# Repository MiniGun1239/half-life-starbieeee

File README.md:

# half-life-starbieeee
Starbie Project for the YSWS Half Life

## What is this
Well, its just a starbie, except shaped like a very badly shaped rocket and a rotary encoder is added.

Its your own PCB Pet... a PetCB

## PCB routing and stuff

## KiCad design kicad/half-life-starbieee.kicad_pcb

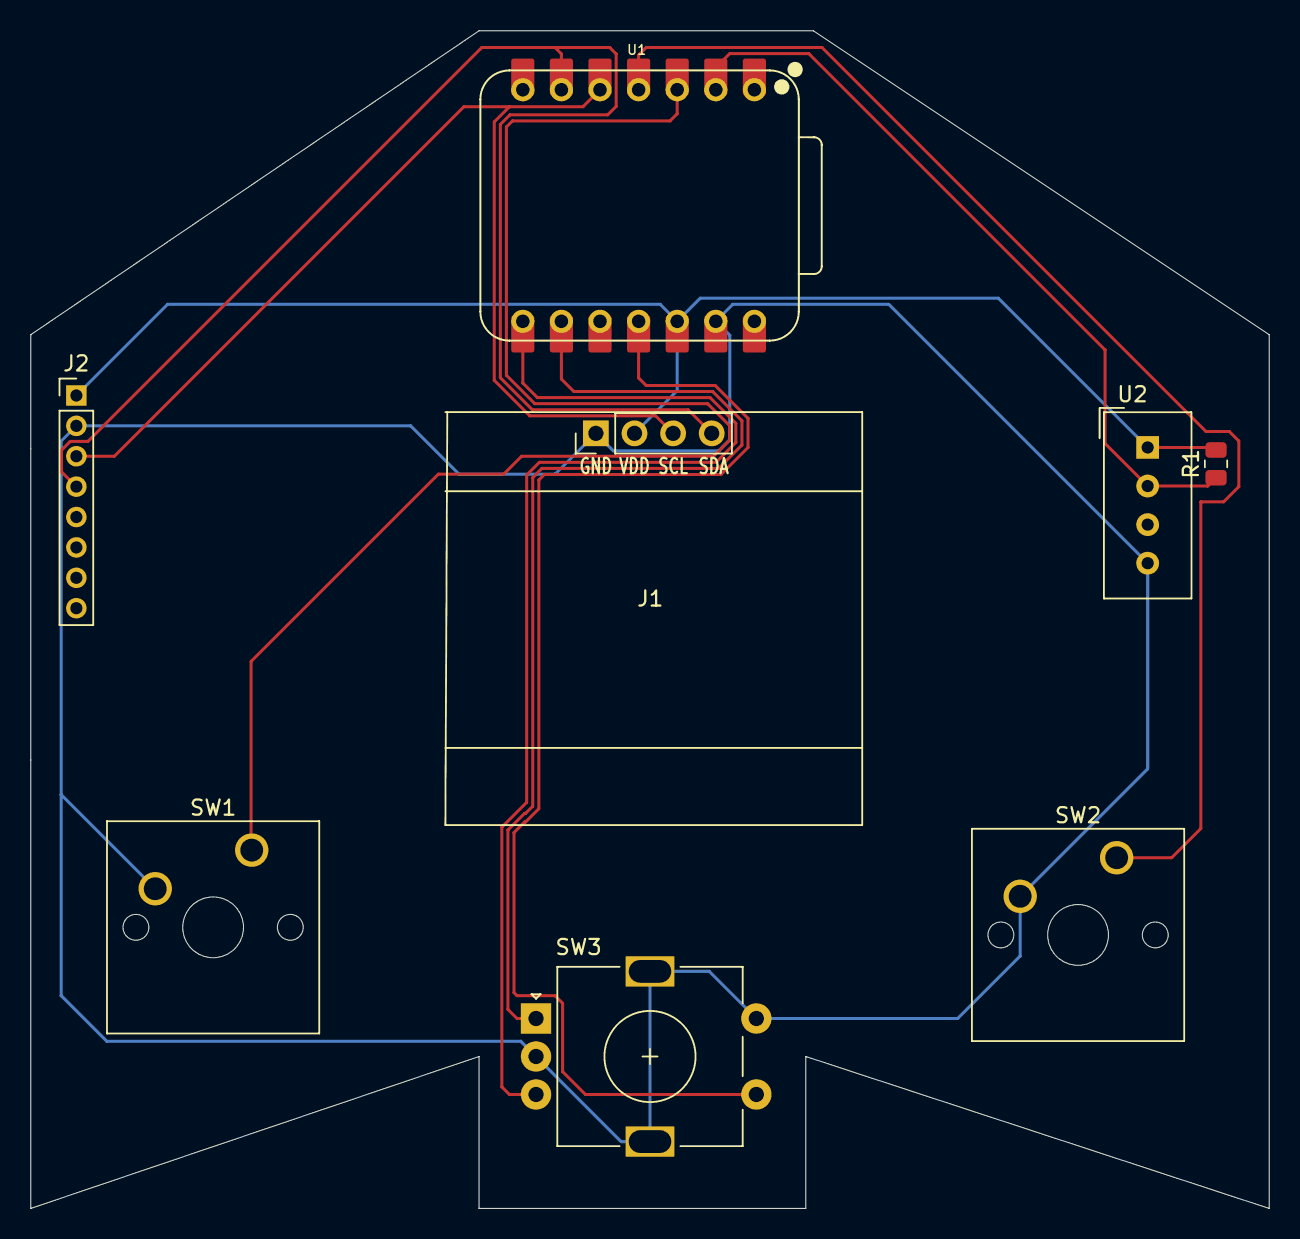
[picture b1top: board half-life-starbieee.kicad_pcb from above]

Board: 2 copper layers, 81.5 x 77.5 mm, 8 parts (0 on the bottom side), 10 nets.

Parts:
J1: Conn_01x04_Pin; Display_128x64_096_I2C
J2: Conn_01x08_Pin; PinHeader_1x08_P2.00mm_Vertical
R1: 10k; R_0805_2012Metric
SW1, SW2: SW_Push; SW_Cherry_MX_1.00u_PCB
SW3: RotaryEncoder_Switch_MP; RotaryEncoder_Alps_EC11E-Switch_Vertical_H20mm
U1: XIAO-ESP32-C3-SMD; XIAO-ESP32-C6-DIP
U2: DHT11; Aosong_DHT11_5.5x12.0_P2.54mm

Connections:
+3.3V: J1.2, J2.1, R1.2, U1.12 (3V3_OUT), U2.1 (VDD)
/B1: SW1.1, U1.3 (D2)
/B2: SW2.1, U1.4 (D3)
/DHT11_DAT: R1.1, U1.2 (D1), U2.2 (DATA)
/RE1_A: SW3.A, U1.9 (D8)
/RE1_B: SW3.B, U1.8 (D7)
/RE_B3: SW3.S1, U1.11 (D10)
/SCL: J1.3, J2.3, U1.5 (D4)
/SDA: J1.4, J2.4, U1.6 (D5)
GND: J1.1, J2.2, SW1.2, SW2.2, SW3.C, SW3.MP, SW3.S2, U1.13 (GND), U2.4 (GND)
